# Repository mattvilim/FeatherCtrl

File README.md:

# Recommended hardware
* [Connectors](https://www.digikey.com/product-detail/en/molex-llc/0039532135/WM14526-ND/3160262)
* [Feather](https://www.adafruit.com/product/4062)

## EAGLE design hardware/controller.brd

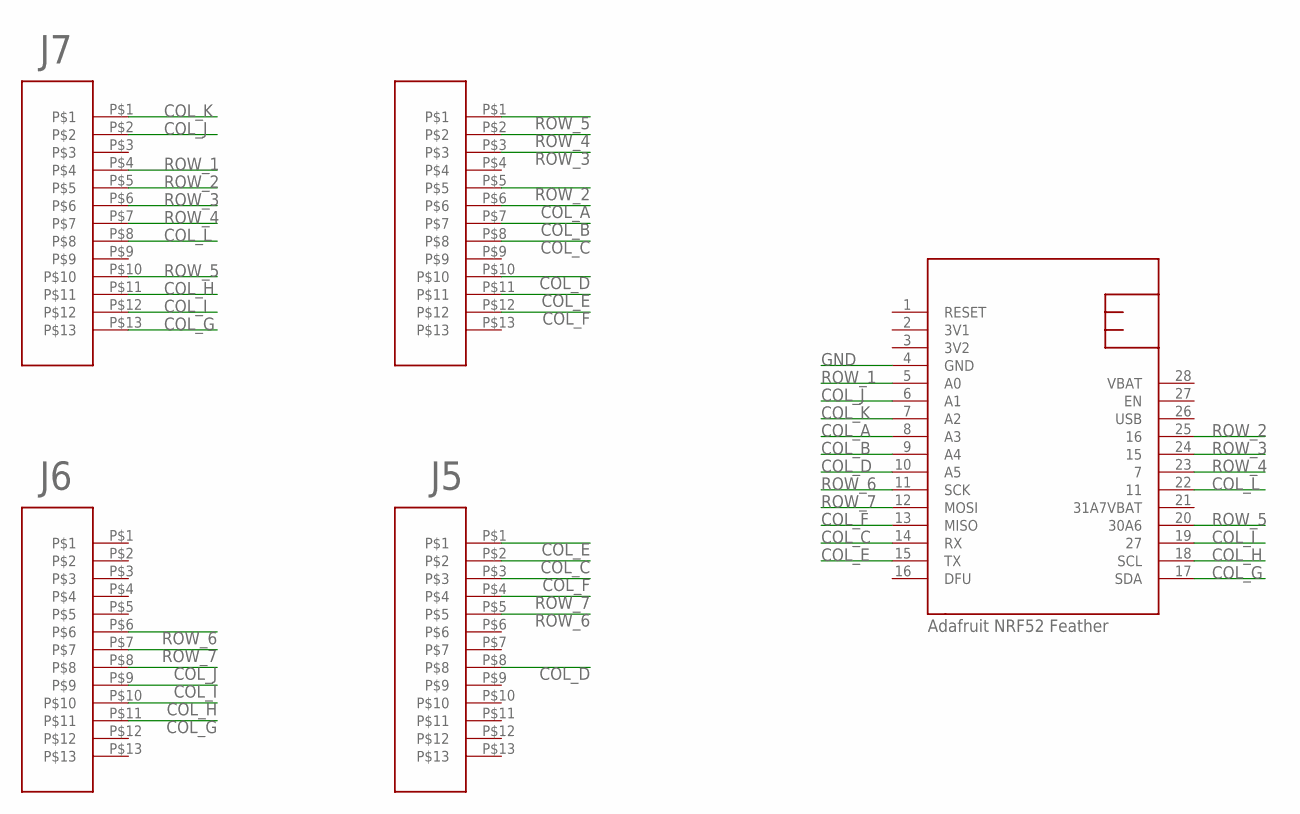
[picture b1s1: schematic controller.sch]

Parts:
U$1: NRF52FEATHER
U$4, U$5, U$6, U$7: TOPLINKS_STAPELBERG

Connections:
3V1: U$1.2 (3V1)
3V2: U$1.3 (3V2)
COL_A: U$1.8 (A3), U$5.P$6
COL_B: U$1.9 (A4), U$5.P$7
COL_C: U$1.14 (RX), U$5.P$8, U$6.P$2
COL_D: U$1.10 (A5), U$5.P$10, U$6.P$8
COL_E: U$1.15 (TX), U$5.P$11, U$6.P$1
COL_F: U$1.13 (MISO), U$5.P$12, U$6.P$3
COL_G: U$1.17 (SDA), U$4.P$13, U$7.P$11
COL_H: U$1.18 (SCL), U$4.P$11, U$7.P$10
COL_I: U$1.19 (27), U$4.P$12, U$7.P$9
COL_J: U$1.6 (A1), U$4.P$2, U$7.P$8
COL_K: U$1.7 (A2), U$4.P$1
COL_L: U$1.22 (11), U$4.P$8
GND: U$1.4 (GND)
ROW_1: U$1.5 (A0), U$4.P$4
ROW_2: U$1.25 (16), U$4.P$5, U$5.P$5
ROW_3: U$1.24 (15), U$4.P$6, U$5.P$3
ROW_4: U$1.23 (7), U$4.P$7, U$5.P$2
ROW_5: U$1.20 (30A6), U$4.P$10, U$5.P$1
ROW_6: U$1.11 (SCK), U$6.P$5, U$7.P$6
ROW_7: U$1.12 (MOSI), U$6.P$4, U$7.P$7
VBAT: U$1.28 (VBAT)

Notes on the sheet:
Adafruit NRF52 Feather

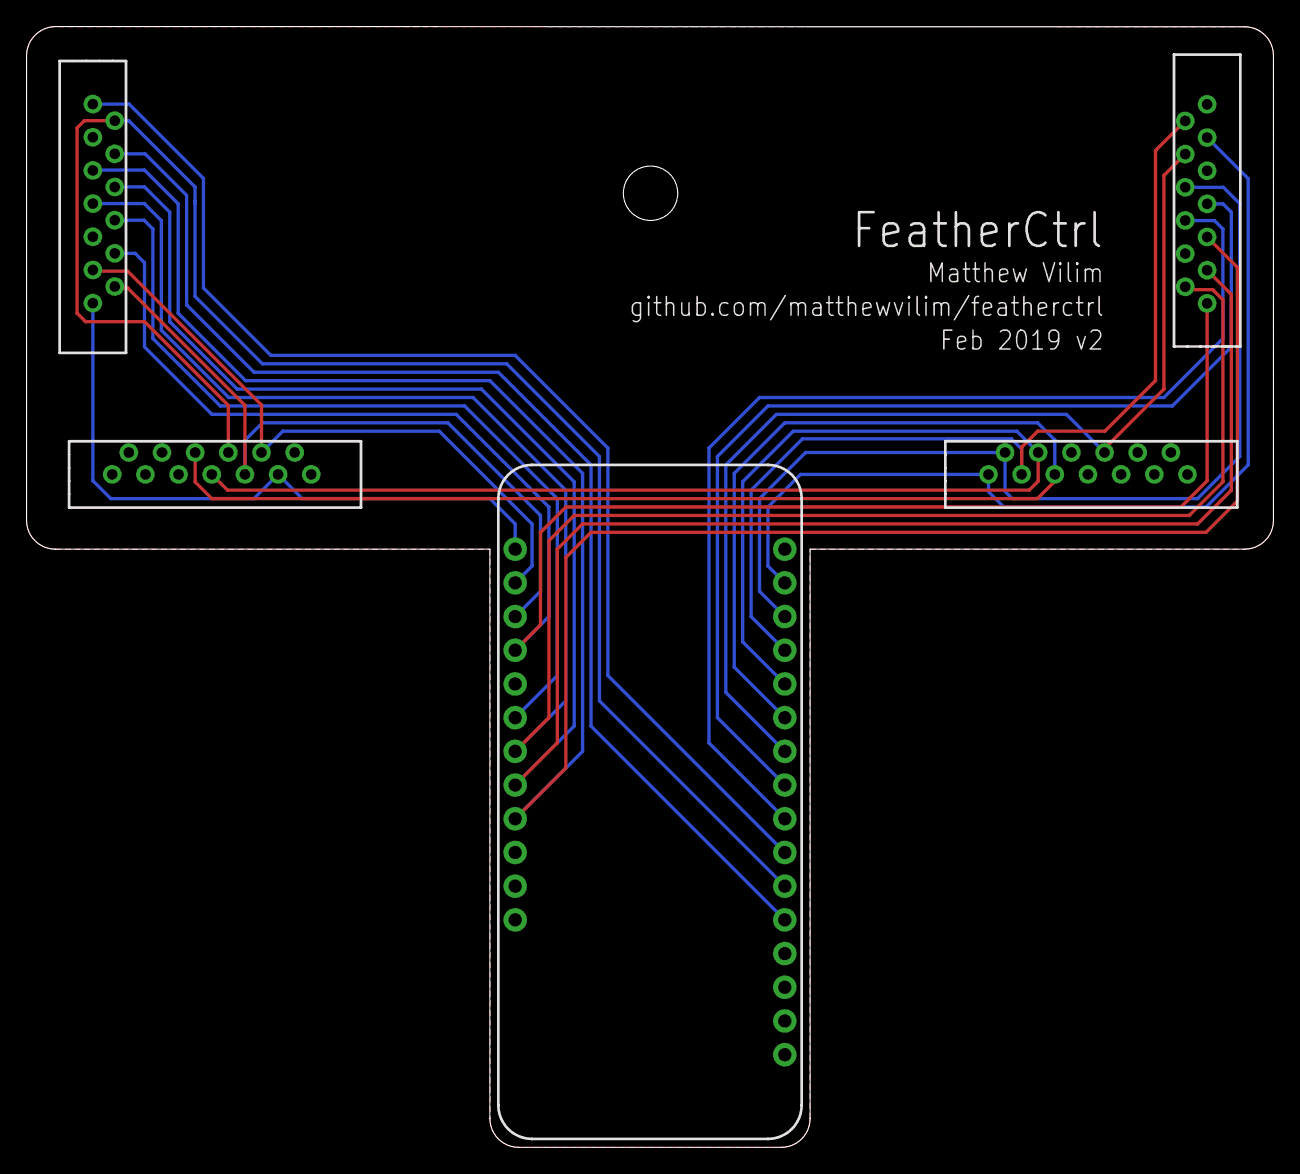
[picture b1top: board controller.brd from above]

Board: 2 copper layers, 94.0 x 84.5 mm, 5 parts (0 on the bottom side), 19 nets.

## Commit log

2019-06-09 Use various key states for debouncing.
2020-03-09 add onshape

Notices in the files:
parts and their libraries:
SparkFun-Aesthetics: Licensing: Creative Commons ShareAlike 4.0 International - https://creativecommons.org/licenses/by-sa/4.0
